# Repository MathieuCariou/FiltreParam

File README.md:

# Filtre audio paramétrique

Cette documentation contient les différents éléments qui permettent de fabriquer le filtre paramétrique proposé :

- Fichiers Eagle (schéma électrique et routage)
- Fichiers Gerber
- Fichier d'implémentation des composants et dimensions
- Procédure de câblage (Wiki)
- Procédure de mise au point de la carte (Wiki)

Le filtre paramétrique proposé est inspiré de celiui proposé par Remy Mallard, Sonelec-musique https://www.sonelec-musique.com/electronique_realisations_filtre_bf_007.html﻿

# Procédure de câblage de la carte
Le câblage consiste à connecter par soudure tous les éléments ensembles (composants, connecteurs, sélecteurs, potentiomètres)
Le câblage de la carte peut être fait en 2 étapes que voici :
﻿
## Etape 1 : Soudure des composants
En suivant le schéma d'implantation présenté précédemment vous pouvez souder, dans l'ordre proposé, les éléments suivants :

1) Les liaisons filaires interne à la carte (aussi appelés strap ou jumper) en utilisants des fils (blanc par exemple)

2) Les résistances

3) les condensateurs

4) les deux supports de circuits intégrés

5) souder les potentiomètres sur la carte.
﻿
## Etape 2 : Câblage des éléments extérieurs
ATTENTION : les pastilles peuvent être fragiles et se décoller facilement, prenez soin d'être délicats !
Il est conseillé de câbler dans un premier temps tout les câbles sur le circuit imprimé. Les éléments extérieurs (connecteurs XLR, sélecteur et potentiomètre seront câblés en dernier)

1) Câbler l'alimentation externe sur la carte de circuit imprimé

* +12V en rouge
* - 12 V en orange
* gnd (la masse) en noir

﻿
2) Souder les fils de l'entrée audio sur la carte de circuit imprimé

* gnd en noir
* Le signal d'entrée en une couleur autre que le rouge ou le orange
* Les fils seront ensuite soudé à l'autre extrémité sur les connecteur XLR lorsque tous les câbles de tous les composants seront soudé à la carte (c'est juste un conseil, aucune obligation

﻿
3) Souder les fils de  sortie audio sur la carte de circuit imprimé

* gnd en noir
* Le signal de sortie en une couleur autre que le rouge ou le orange

﻿4) Souder les fils de l'inverseur dans des couleurs non-utilisés

5) Souder les fils des potentiométres

6) Souder enfin les connecteurs XLR, le sélecteur et les potentiomètres.

# Liste des composants nécéssaires
### Résistances

* 100 Ohm x1 (R4)
* 2k2 Ohm x1 (R8)
* 3k9 Ohm x1 (R11 et R12)
* 10k x 2 (R13, R15)
* 11k Ohm x1 (R16)
* 51k Ohm x 2 (R5 et R4)
* 100k Ohm x7 (R1, R2, R3, R6, R7, R9, R10)

### Condensateurs

* 1nF x2 (C2,C 3)
* 10 nF x2 (C4 et C5)
* 220 nF (C1)

### Potentiomètres

* 100k x1  (potentiomètre double) (RV3)
* 22k x1  (potentiomètre Simple Linéaire) (RV1)
* 100 k Ohm  (Potentiomètre simple logarithmique) (RV2)

﻿
### Amplificateurs opérationnels et leurs supports

    1	TL082P			
1	support DIL08
    1	TL084P	
    1 support 	DIL14	U2	OP AMP	avec son support

﻿
Inverseur

    Inverseur 2P2T
    l'interrupteur étant déporté, il faut utiliser du cable souple

﻿
Du câble souple pour :

    Câbles souples pour l'interrupteur
    -12 (orange)  +12(rouge)   gnd (noir)
    gnd (noir)  entr√©e	PINHD-1X2	1X02	J_IN	PIN HEADER
    sortie   gnd(noir)	PINHD-1X2	1X02	J_OUT	PIN HEADER

﻿
﻿
Du câble rigide pour les jumpers

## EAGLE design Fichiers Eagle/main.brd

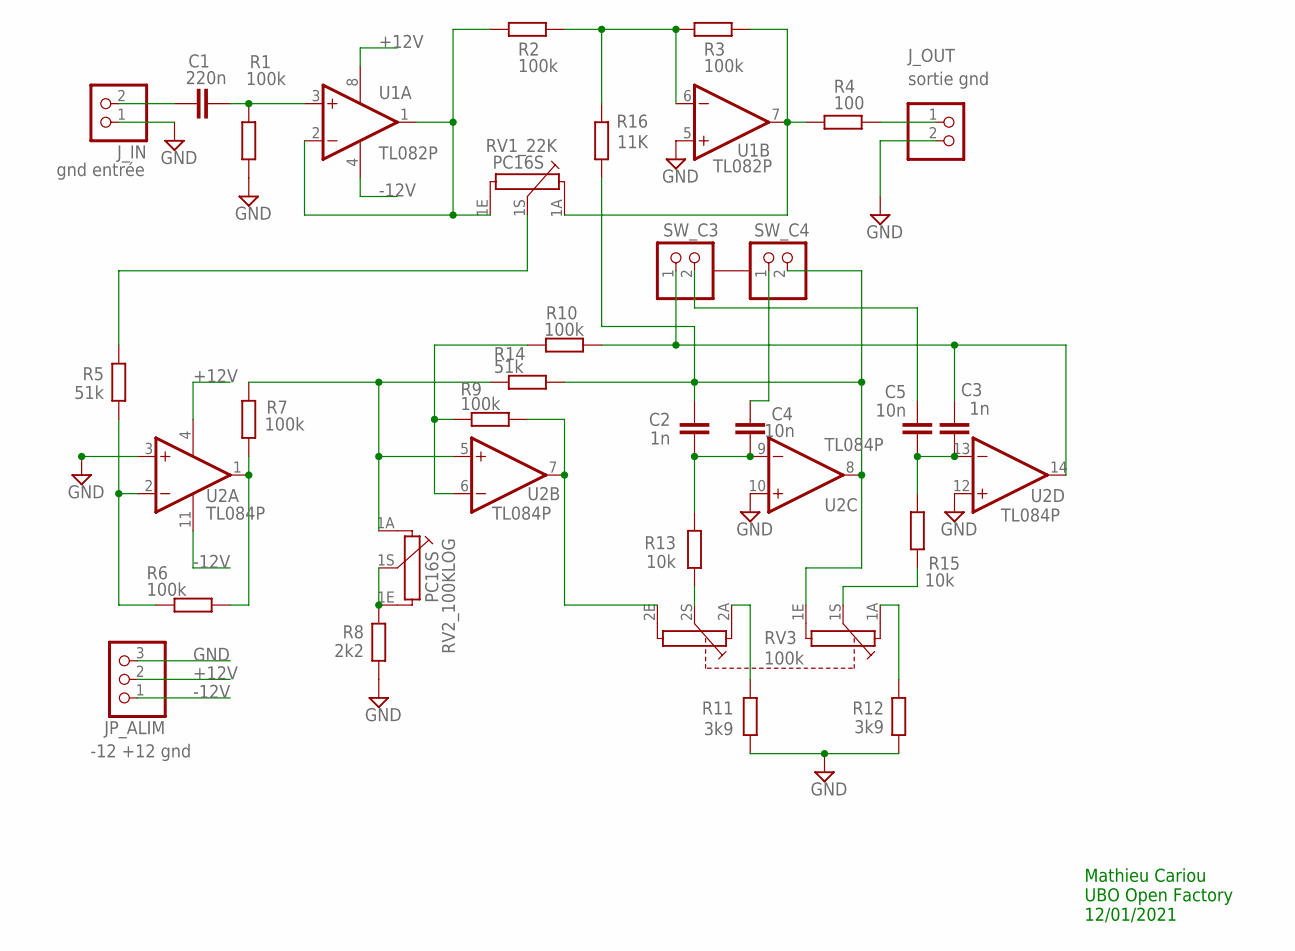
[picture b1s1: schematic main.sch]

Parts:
C1: 220n; C050-030X075
C2, C3: 1n; C050-030X075
C4, C5: 10n; C050-030X075
JP_ALIM: -12 +12 gnd; 1X03
J_IN: gnd entrée; 1X02
J_OUT: sortie gnd; 1X02
R1, R2, R3, R6, R7, R9, R10: 100k; 0204/7
R4: 100; 0204/7
R5, R14: 51k; 0204/7
R8: 2k2; 0204/7
R11, R12: 3k9; 0204/7
R13, R15: 10k; 0204/7
R16: 11K; 0204/7
RV1_22K, RV2_100KLOG: PC16S
RV3: 100k; PC16D
SW_C3, SW_C4: PINHD-1X2; 1X02
U1: TL082P; DIL08
U2: TL084P; DIL14

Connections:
+12V: JP_ALIM.2, U1.8 (V+), U2.4 (V+)
-12V: JP_ALIM.1, U1.4 (V-), U2.11 (V-)
GND: JP_ALIM.3, J_IN.1, J_OUT.2, R1.1, R8.1, R11.1, R12.1, U1.5 (+IN), U2.3 (+IN), U2.10 (+IN), U2.12 (+IN)
unnamed: C1.2, R1.2, U1.3 (+IN)
unnamed: R2.1, RV1_22K.1E, U1.1 (OUT), U1.2 (-IN)
unnamed: R3.2, R4.1, RV1_22K.1A, U1.7 (OUT)
unnamed: R2.2, R3.1, R16.2, U1.6 (-IN)
unnamed: C2.2, R14.2, R16.1, RV3.1E, SW_C4.2, U2.8 (OUT)
unnamed: C1.1, J_IN.2
unnamed: J_OUT.1, R4.2
unnamed: R5.2, RV1_22K.1S
unnamed: R5.1, R6.1, U2.2 (-IN)
unnamed: R6.2, R7.1, U2.1 (OUT)
unnamed: R9.1, R10.1, U2.6 (-IN)
unnamed: R7.2, R14.1, RV2_100KLOG.1A, U2.5 (+IN)
unnamed: R8.2, RV2_100KLOG.1E, RV2_100KLOG.1S
unnamed: R9.2, RV3.2E, U2.7 (OUT)
unnamed: R11.2, RV3.2A
unnamed: R12.2, RV3.1A
unnamed: R13.1, RV3.2S
unnamed: R15.1, RV3.1S
unnamed 21: C3.2, R10.2, SW_C3.1, U2.14 (OUT); also elsewhere on the board
unnamed: C2.1, C4.1, R13.2, U2.9 (-IN)
unnamed: C3.1, C5.1, R15.2, U2.13 (-IN)
unnamed: C4.2, SW_C4.1
unnamed 25: C5.2, SW_C3.2; also elsewhere on the board

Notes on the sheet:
Mathieu Cariou UBO Open Factory 12/01/2021

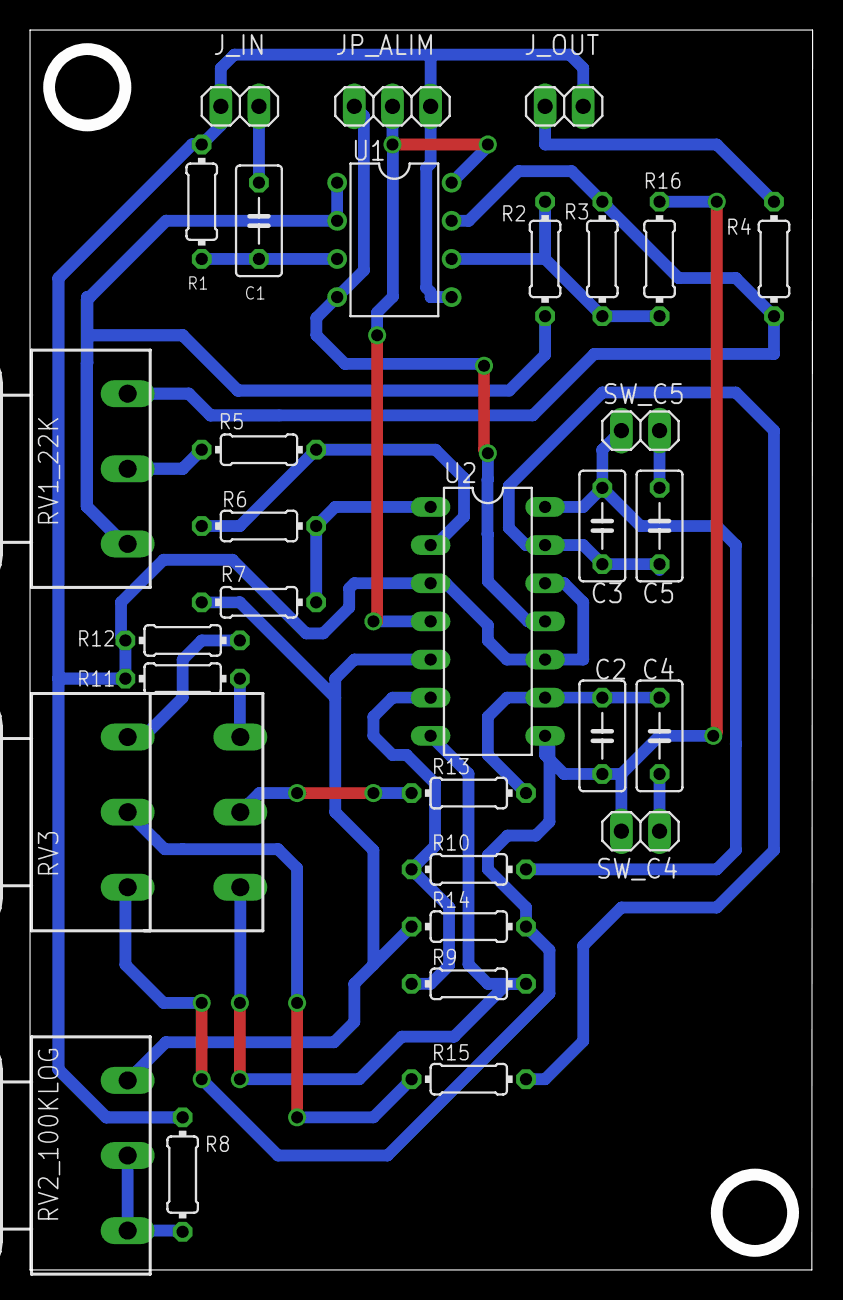
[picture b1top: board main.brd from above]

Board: 2 copper layers, 51.3 x 81.8 mm, 31 parts (0 on the bottom side), 26 nets.

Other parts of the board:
SW_C5: 1X02

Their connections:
unnamed 21: SW_C5.1; also elsewhere on the board
unnamed 25: SW_C5.2; also elsewhere on the board

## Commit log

2021-11-05 Ajout des fichier 2020
2021-11-05 modif espacement Potentiomètre
    espacement à à 22.86 mm
2021-11-05 suppresion fichiers temporaire eagle
2021-11-05 suppression des fichier lock
2021-11-05 Ajout implementation et dimmension
    - ajout implementation et dimension
    - suppression des anciens fichiers
2021-11-05 ajout Readme principal
2021-11-05 mise à jour readme
    - câblage des éléments
2021-11-05 ajout liste composant dans readme
2022-01-12 ajout cartouche
2022-01-12 mise à jour cartouche Schematic
2022-01-12 mise à jour pdf sch
2022-01-12 remplacement SWC3 par SWC5
2022-01-12 mise à jour implantation et routage
